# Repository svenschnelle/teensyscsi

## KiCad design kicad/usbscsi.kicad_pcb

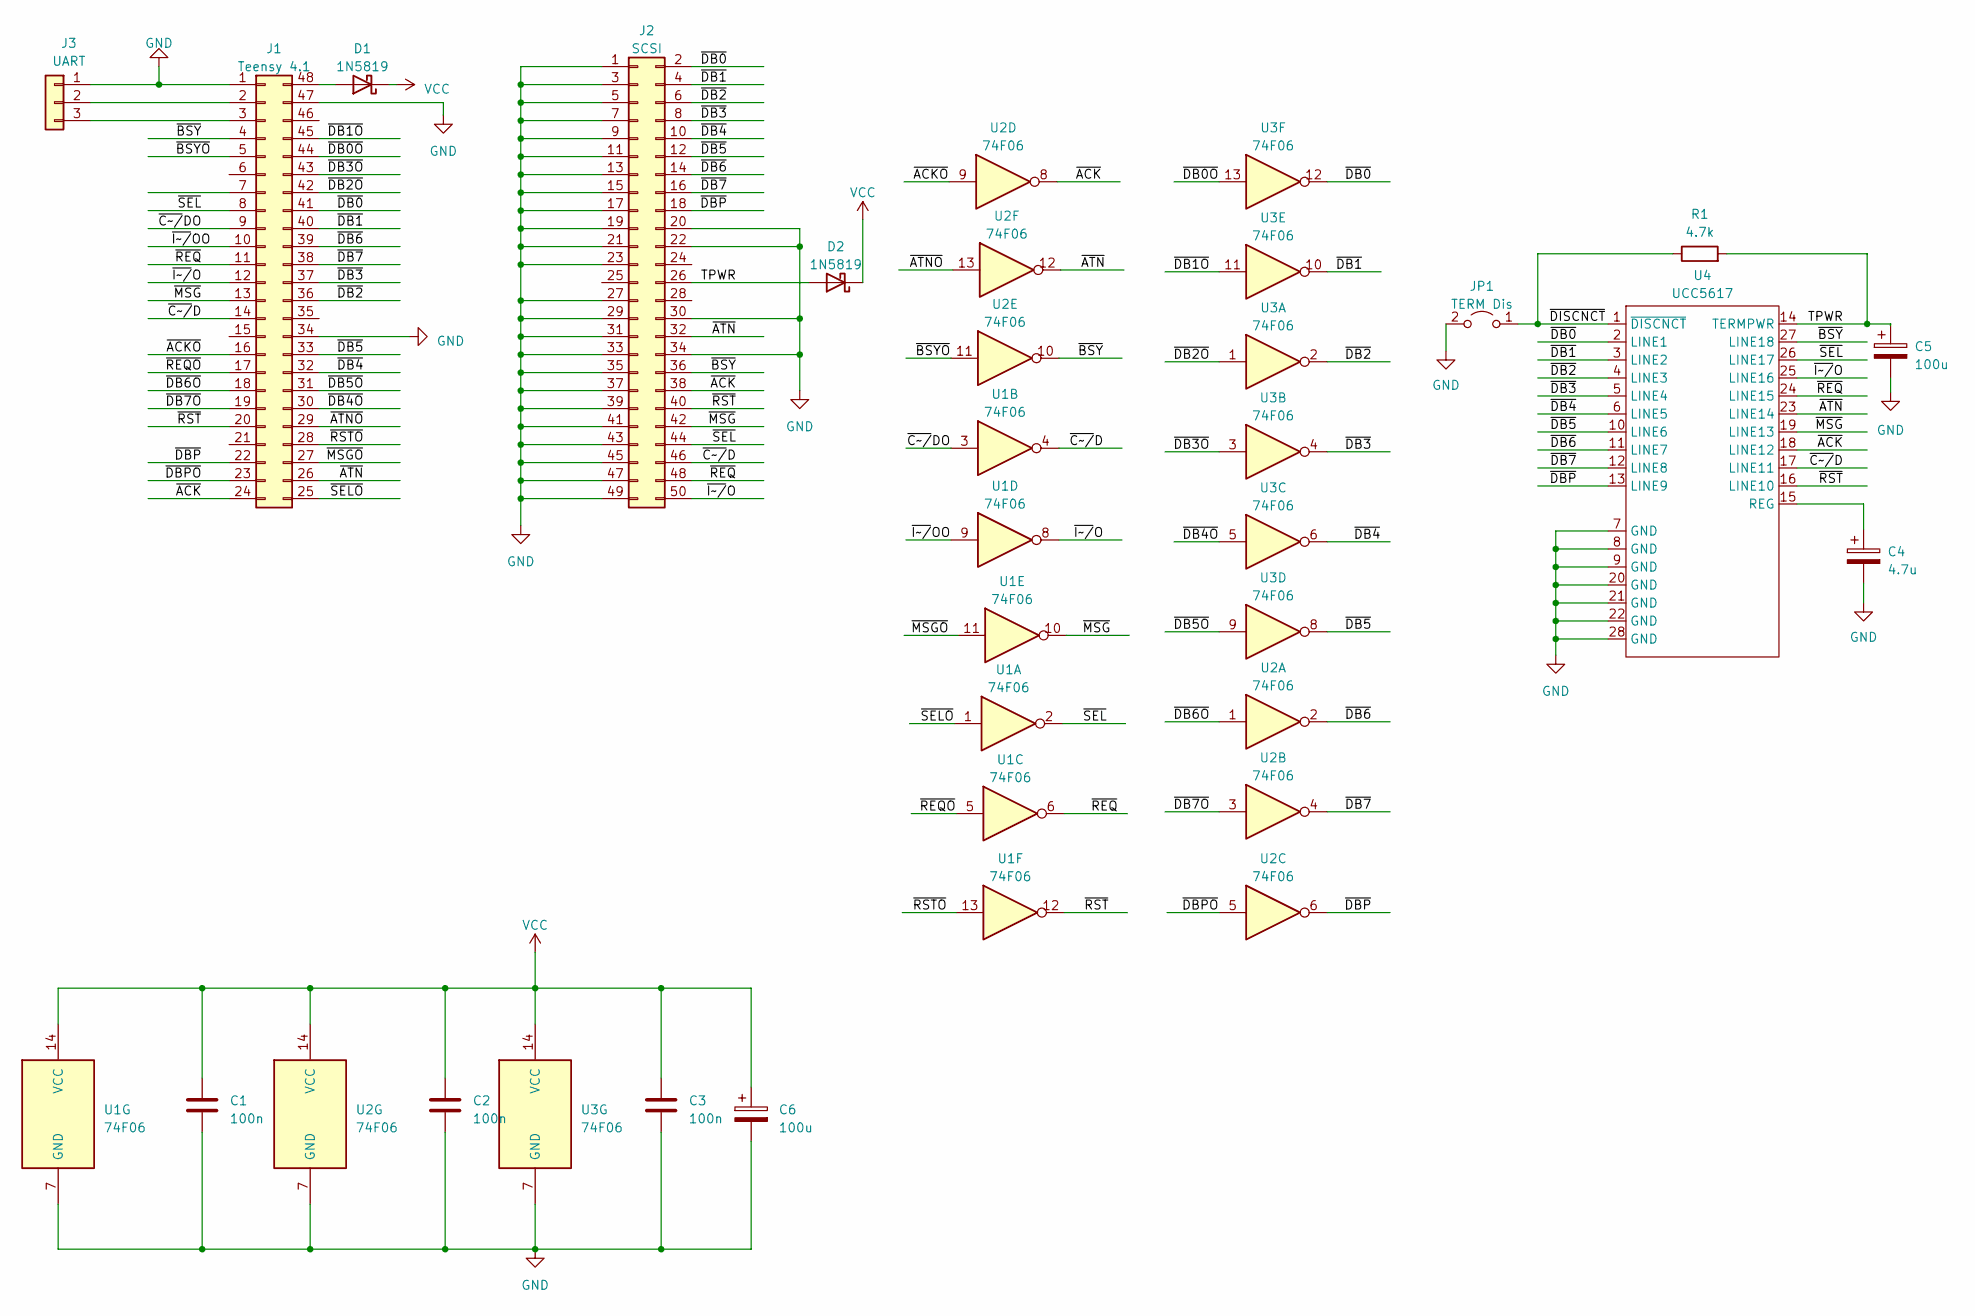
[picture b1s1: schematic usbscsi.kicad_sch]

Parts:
C1, C2, C3: 100n; C_0603_1608Metric
C4: 4.7u; CP_Radial_D5.0mm_P2.50mm
C5: 100u; CP_Radial_D5.0mm_P2.50mm
C6: 100u; CP_Radial_D6.3mm_P2.50mm
D1, D2: 1N5819; D_DO-41_SOD81_P10.16mm_Horizontal
J1: Teensy 4.1; DIP-48_W15.24mm_LongPads
J2: SCSI; PinHeader_2x25_P2.54mm_Vertical
J3: UART; PinHeader_1x03_P2.54mm_Vertical
JP1: TERM Dis; TestPoint_2Pads_Pitch2.54mm_Drill0.8mm
R1: 4.7k; R_0603_1608Metric
U1, U2, U3: 74F06; SO-14_3.9x8.65mm_P1.27mm
U4: UCC5617; SOIC-28W_7.5x17.9mm_P1.27mm

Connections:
/TPWR: C5.1, D2.2 (A), J2.26, R1.2, U4.14 (TERMPWR)
/~ACKO~: J1.16, U2.9
/~ACK~: J1.24, J2.38, U2.8, U4.18 (LINE12)
/~ATNO~: J1.29, U2.13
/~ATN~: J1.26, J2.32, U2.12, U4.23 (LINE14)
/~BSYO~: J1.5, U2.11
/~BSY~: J1.4, J2.36, U2.10, U4.27 (LINE18)
/~C~/D: J1.14, J2.46, U1.4, U4.17 (LINE11)
/~C~/DO: J1.9, U1.3
/~DB0O~: J1.44, U3.13
/~DB0~: J1.41, J2.2, U3.12, U4.2 (LINE1)
/~DB1O~: J1.45, U3.11
/~DB1~: J1.40, J2.4, U3.10, U4.3 (LINE2)
/~DB2O~: J1.42, U3.1
/~DB2~: J1.36, J2.6, U3.2, U4.4 (LINE3)
/~DB3O~: J1.43, U3.3
/~DB3~: J1.37, J2.8, U3.4, U4.5 (LINE4)
/~DB4O~: J1.30, U3.5
/~DB4~: J1.32, J2.10, U3.6, U4.6 (LINE5)
/~DB5O~: J1.31, U3.9
/~DB5~: J1.33, J2.12, U3.8, U4.10 (LINE6)
/~DB6O~: J1.18, U2.1
/~DB6~: J1.39, J2.14, U2.2, U4.11 (LINE7)
/~DB7O~: J1.19, U2.3
/~DB7~: J1.38, J2.16, U2.4, U4.12 (LINE8)
/~DBPO~: J1.23, U2.5
/~DBP~: J1.22, J2.18, U2.6, U4.13 (LINE9)
/~DISCNCT~: JP1.1 (A), R1.1, U4.1 (~DISCNCT~)
/~I~/O: J1.12, J2.50, U1.8, U4.25 (LINE16)
/~I~/OO: J1.10, U1.9
/~MSGO~: J1.27, U1.11
/~MSG~: J1.13, J2.42, U1.10, U4.19 (LINE13)
/~REQO~: J1.17, U1.5
/~REQ~: J1.11, J2.48, U1.6, U4.24 (LINE15)
/~RSTO~: J1.28, U1.13
/~RST~: J1.20, J2.40, U1.12, U4.16 (LINE10)
/~SELO~: J1.25, U1.1
/~SEL~: J1.8, J2.44, U1.2, U4.26 (LINE17)
GND: C1.2, C2.2, C3.2, C4.2, C5.2, C6.2, J1.1, J1.34, J1.47, J2.1, J2.3, J2.5, J2.7, J2.9, J2.11, J2.13, J2.15, J2.17, J2.19, J2.20, J2.21, J2.22, J2.23, J2.27, J2.29, J2.30, J2.31, J2.33, J2.34, J2.35, J2.37, J2.39, J2.41, J2.43, J2.45, J2.47, J2.49, J3.1, JP1.2 (B), U1.7 (GND), U2.7 (GND), U3.7 (GND), U4.7 (GND), U4.8 (GND), U4.9 (GND), U4.20 (GND), U4.21 (GND), U4.22 (GND), U4.28 (GND)
unnamed: C4.1, U4.15 (REG)
unnamed: D1.2 (A), J1.48
unnamed: J1.2, J3.2
unnamed: J1.3, J3.3
VCC: C1.1, C2.1, C3.1, C6.1, D1.1 (K), D2.1 (K), U1.14 (VCC), U2.14 (VCC), U3.14 (VCC)

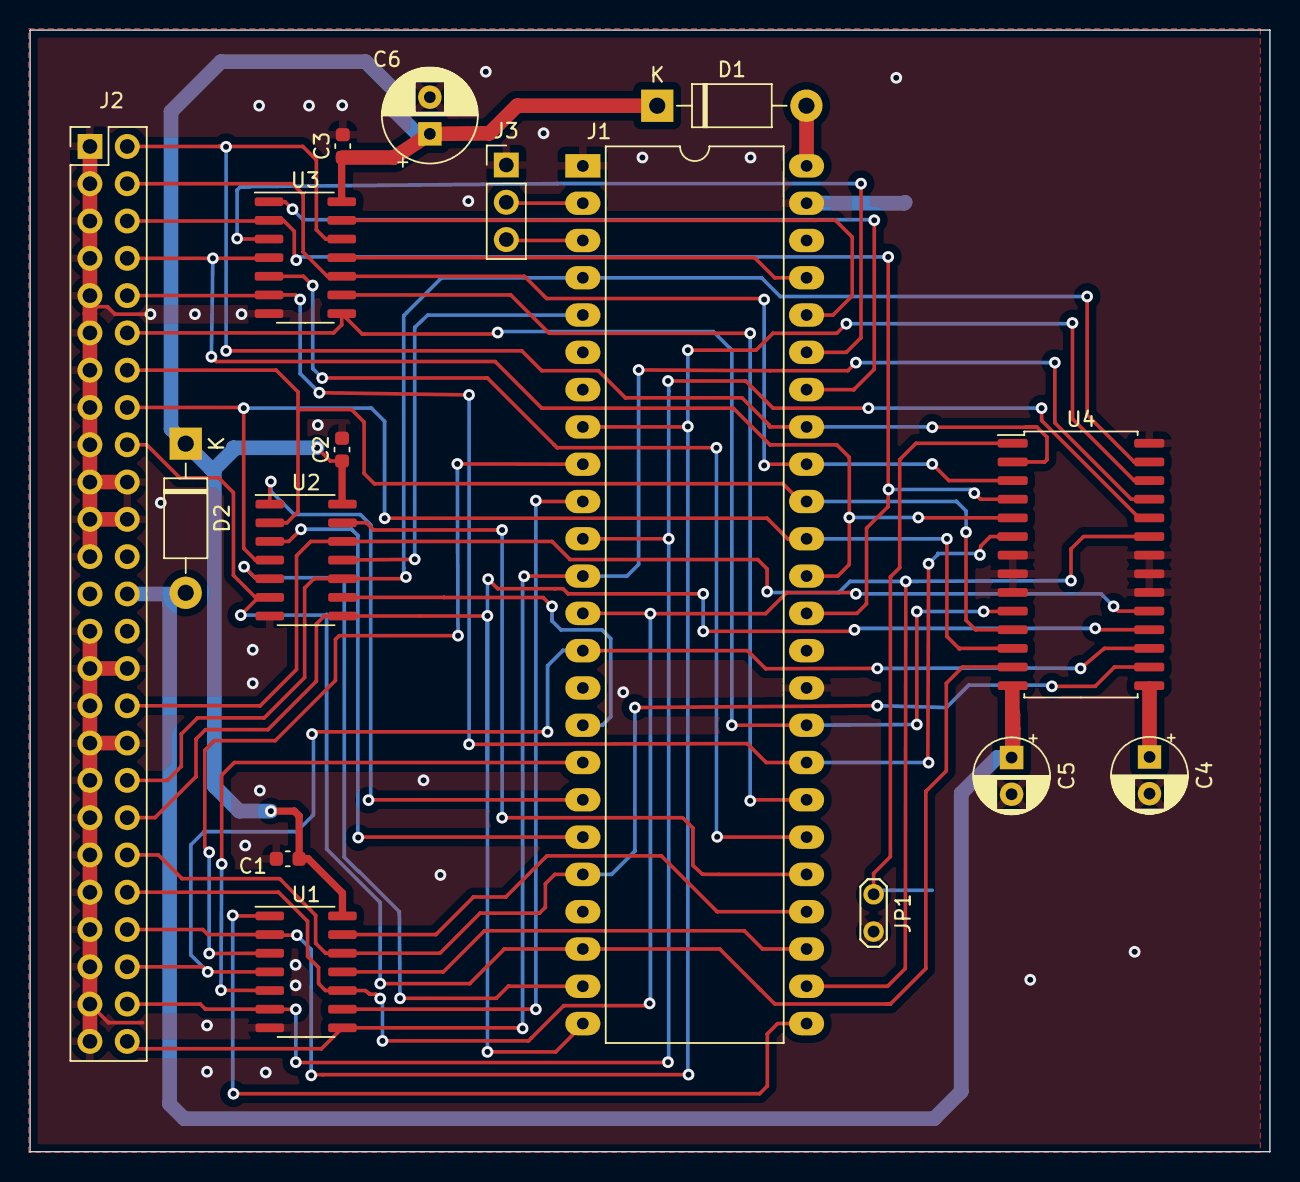
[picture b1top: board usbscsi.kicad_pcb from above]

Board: 2 copper layers, 84.4 x 76.4 mm, 17 parts (1 on the bottom side), 44 nets.

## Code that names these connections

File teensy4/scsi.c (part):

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#include <Arduino.h>

#define BSYI_PIN 2
#define BSYO_PIN 3
#define SELI_PIN 6
#define CDO_PIN 7
#define IOO_PIN 8
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#define IOI_PIN 10
#define MSGI_PIN 11
#define CDI_PIN 12
#define ACKO_PIN 24
#define REQO_PIN 25
#define DB6O_PIN 26
#define DB7O_PIN 27
#define RSTI_PIN 28
#define DBPI_PIN 30
#define DBPO_PIN 31
#define ACKI_PIN 32
#define SELO_PIN 33
#define ATNI_PIN 34
#define MSGO_PIN 35
#define RSTO_PIN 36
#define ATNO_PIN 37
#define DB4O_PIN 38
#define DB5O_PIN 39
#define DB4I_PIN 40
#define DB5I_PIN 41
#define DB2I_PIN 14
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#define DB6I_PIN 17
#define DB1I_PIN 18
#define DB0I_PIN 19
#define DB2O_PIN 20
#define DB3O_PIN 21
#define DB0O_PIN 22
#define DB1O_PIN 23

#define LED_PIN 13
#define SCSI_BUS_CLEAR_DELAY 800
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	pinMode(DB7I_PIN, INPUT);
	pinMode(DBPI_PIN, INPUT);

	digitalWriteFast(SELO_PIN, LOW);
	digitalWriteFast(BSYO_PIN, LOW);
	digitalWriteFast(RSTO_PIN, LOW);
	digitalWriteFast(REQO_PIN, LOW);
	digitalWriteFast(ACKO_PIN, LOW);
	digitalWriteFast(CDO_PIN, LOW);
	digitalWriteFast(IOO_PIN, LOW);
	digitalWriteFast(MSGO_PIN, LOW);
	digitalWriteFast(ATNO_PIN, LOW);

	digitalWriteFast(DB0O_PIN, LOW);
	digitalWriteFast(DB1O_PIN, LOW);
	digitalWriteFast(DB2O_PIN, LOW);
	digitalWriteFast(DB3O_PIN, LOW);
	digitalWriteFast(DB4O_PIN, LOW);
	digitalWriteFast(DB5O_PIN, LOW);
	digitalWriteFast(DB6O_PIN, LOW);
	digitalWriteFast(DB7O_PIN, LOW);
	digitalWriteFast(DBPO_PIN, LOW);

	pinMode(SELO_PIN, OUTPUT);
	pinMode(BSYO_PIN, OUTPUT);
	pinMode(RSTO_PIN, OUTPUT);
	pinMode(REQO_PIN, OUTPUT);
	pinMode(ACKO_PIN, OUTPUT);
	pinMode(CDO_PIN, OUTPUT);
	pinMode(IOO_PIN, OUTPUT);
	pinMode(MSGO_PIN, OUTPUT);
	pinMode(ATNO_PIN, OUTPUT);

	pinMode(DB0O_PIN, OUTPUT);
	pinMode(DB1O_PIN, OUTPUT);
	pinMode(DB2O_PIN, OUTPUT);
	pinMode(DB3O_PIN, OUTPUT);
	pinMode(DB4O_PIN, OUTPUT);
	pinMode(DB5O_PIN, OUTPUT);
	pinMode(DB6O_PIN, OUTPUT);
	pinMode(DB7O_PIN, OUTPUT);
	pinMode(DBPO_PIN, OUTPUT);

	pinMode(LED_PIN, OUTPUT);
}
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static void scsi_set_hiz(void)
{
	GPIO6_DR_CLEAR |= (0xff << 24);
	digitalWriteFast(DBPO_PIN, LOW);
}

static void scsi_set_data(uint8_t data)
{
	GPIO6_DR_CLEAR |= ~data << 24;
	GPIO6_DR_SET |= data << 24;
	digitalWriteFast(DBPO_PIN, parity_table[data]);
}

static __attribute__((unused)) void dump_scsi(const char *prefix)
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	// XX SEL BSY RST ACK REQ CD IO MSG ATN
	SCSI_DEBUG(SCSI_DEBUG_PIN, "%s: %02X %s%s%s%s%s%s%s%s%s%s\n",
	       prefix, scsi_get_data(),
	       digitalReadFast(SELI_PIN) ? "" : "SEL ",
	       digitalReadFast(BSYI_PIN) ? "" : "BSY ",
	       digitalReadFast(RSTI_PIN) ? "" : "RST ",
	       digitalReadFast(ACKI_PIN) ? "" : "ACK ",
	       digitalReadFast(REQI_PIN) ? "" : "REQ ",
	       digitalReadFast(CDI_PIN) ? "" : "CD ",
	       digitalReadFast(IOI_PIN) ? "" : "IO ",
	       digitalReadFast(MSGI_PIN) ? "" : "MSG ",
	       digitalReadFast(ATNI_PIN) ? "" : "ATN ",
	       digitalReadFast(DBPI_PIN) ? "" : "DBP ");
}

void scsi_reset(void)
{
	digitalWriteFast(RSTO_PIN, HIGH);
	scsi_set_hiz();
        digitalWriteFast(SELO_PIN, LOW);
	digitalWriteFast(BSYO_PIN, LOW);
	digitalWriteFast(ACKO_PIN, LOW);
	digitalWriteFast(REQO_PIN, LOW);
	digitalWriteFast(CDO_PIN, LOW);
	digitalWriteFast(IOO_PIN, LOW);
        digitalWriteFast(MSGO_PIN, LOW);
	digitalWriteFast(ATNO_PIN, LOW);
	delay(10);
	digitalWriteFast(RSTO_PIN, LOW);
	delay(250);
	memset(&scsi_tags, 0, sizeof(scsi_tags));
}
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static int scsi_wait_bus_free(void)
{
	for(;;) {
		digitalWriteFast(BSYO_PIN, LOW);
		delayNanoseconds(800); /* Bus clear delay */
		while(!(digitalReadFast(SELI_PIN) & digitalReadFast(BSYI_PIN)));
		/* start arbitration */
		digitalWriteFast(BSYO_PIN, HIGH);
		scsi_set_data(sctx.hostidmsk);
		delayNanoseconds(2400); /* Arbitration delay */
		if (!(scsi_get_data() & (sctx.hostidmsk-1)))
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{
	int i = 250000000 / SCSI_BUS_SETTLE_DELAY;

	digitalWriteFast(SELO_PIN, HIGH);
	if (xfer->outmsgcnt)
		digitalWriteFast(ATNO_PIN, HIGH);
	delayNanoseconds(10 * SCSI_BUS_SETTLE_DELAY);
        scsi_set_data(sctx.hostidmsk | (1 << id));
	delayNanoseconds(10 * SCSI_BUS_SETTLE_DELAY);
	digitalWriteFast(BSYO_PIN, LOW);
	delayNanoseconds(10 * SCSI_BUS_SETTLE_DELAY);

        while (i-- > 0 && digitalReadFast(BSYI_PIN))
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
	if (i < 0) {
		SCSI_DEBUG(SCSI_DEBUG_PHASE, "select failed\n");
		digitalWriteFast(SELO_PIN, LOW);
		return 1;
	}
	xfer->id = id;
        digitalWriteFast(SELO_PIN, LOW);
	delayNanoseconds(SCSI_BUS_SETTLE_DELAY);
	SCSI_DEBUG(SCSI_DEBUG_PHASE, "selected target %d\n", id);
	return 0;
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
static void scsi_ack_async(void)
{
	digitalWriteFast(ACKO_PIN, HIGH);
	while(!digitalReadFast(REQI_PIN));
	digitalWriteFast(ACKO_PIN, LOW);
}

static void scsi_handle_cmd(struct scsi_xfer *xfer)
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			break;

		if (xfer->outmsgpos + 1 == xfer->outmsgcnt) {
			digitalWriteFast(ATNO_PIN, LOW);
		}

		uint8_t msg = xfer->outmsgs[xfer->outmsgpos++];
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	SCSI_DEBUG_NOH(SCSI_DEBUG_DUMP, "\n");
}

static int scsi_msg_length(const uint8_t *msg, int len)
{
	switch(msg[0]) {
	case 0x01:
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				xfer->outmsgs[0] = SCSI_MSG_ABORT;
				xfer->outmsgpos = 0;
				xfer->outmsgcnt = 1;
				digitalWriteFast(ATNO_PIN, HIGH);
				return;
			}
			break;
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		if (ids & sctx.hostidmsk) {
			xfer.id = __builtin_ctz(ids & (sctx.hostidmsk-1));
			SCSI_DEBUG(SCSI_DEBUG_PHASE, "reselection from ID %d\n", xfer.id);
			digitalWriteFast(BSYO_PIN, HIGH);
			while(!digitalReadFast(SELI_PIN));
			digitalWriteFast(BSYO_PIN, LOW);
			delayNanoseconds(SCSI_BUS_SETTLE_DELAY);
			while(!digitalReadFast(BSYI_PIN))
				scsi_handle_phase(&xfer);
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
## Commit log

2021-06-27 Initial revison of Teensy USB SCSI controller
    Very experimental code, reads and writes on Linux.
2021-06-27 avoid memcpy of request cmd ui
2021-06-27 simplify parity lookup
2021-06-27 speed up selection
2021-06-27 move check whether target is still connected
2021-06-28 experimental disconnect/tag support
2021-06-29 remove delays, add scsi_set_hiz()
2021-07-01 msc support and uas for windows
2021-07-01 add schematics/pcb as pdf
2021-07-02 add tag handling
2021-07-03 - use LIST_END for tx descriptor lists - don't ack ZLP packets
